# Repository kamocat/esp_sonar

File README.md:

# esp_sonar
Increased accuracy sonar by using esp32 for signal processing

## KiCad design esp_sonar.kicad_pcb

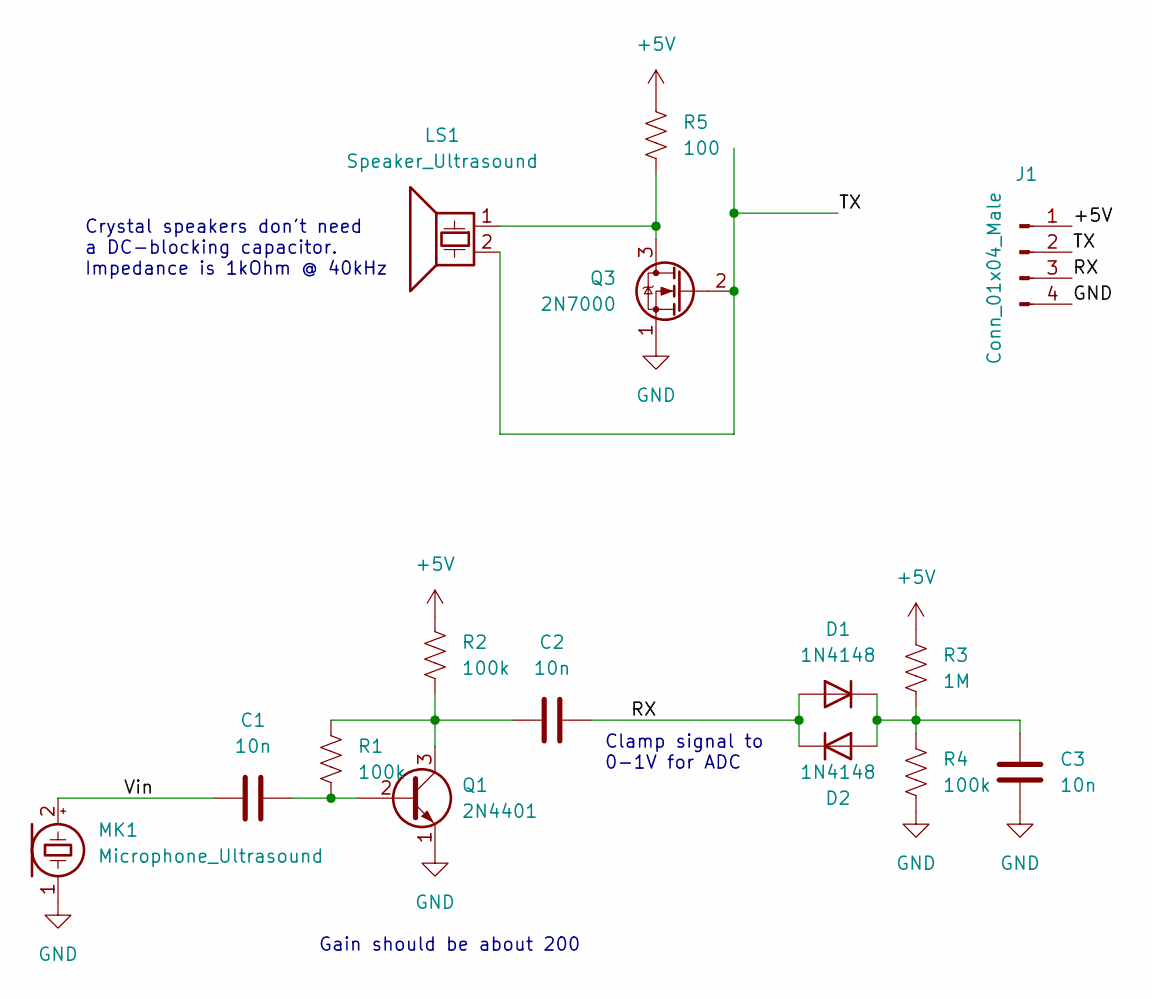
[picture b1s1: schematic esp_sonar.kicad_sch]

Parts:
C1, C2, C3: 10n; C_Disc_D4.7mm_W2.5mm_P5.00mm
D1, D2: 1N4148; D_DO-35_SOD27_P7.62mm_Horizontal
J1: Conn_01x04_Male; PinHeader_1x04_P2.54mm_Horizontal
LS1: Speaker_Ultrasound; PinHeader_1x02_P2.54mm_Vertical
MK1: Microphone_Ultrasound; PinHeader_1x02_P2.54mm_Vertical
Q1: 2N4401; TO-92_Inline_Wide
Q3: 2N7000; TO-92_Inline
R1, R2, R4: 100k; R_Axial_DIN0207_L6.3mm_D2.5mm_P10.16mm_Horizontal
R3: 1M; R_Axial_DIN0207_L6.3mm_D2.5mm_P10.16mm_Horizontal
R5: 100; R_Axial_DIN0207_L6.3mm_D2.5mm_P5.08mm_Vertical

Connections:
+5V: J1.1, R2.1, R3.1, R5.1
/RX: C2.2, D1.2 (A), D2.1 (K), J1.3
/TX: J1.2, LS1.2, Q3.2 (G)
/Vin: C1.1, MK1.2 (+)
GND: C3.2, J1.4, MK1.1 (-), Q1.1 (E), Q3.1 (S), R4.2
unnamed: C1.2, Q1.2 (B), R1.2
unnamed: C2.1, Q1.3 (C), R1.1, R2.2
unnamed: C3.1, D1.1 (K), D2.2 (A), R3.2, R4.1
unnamed: LS1.1, Q3.3 (D), R5.2

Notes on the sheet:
Clamp signal to 0-1V for ADC
Crystal speakers don't need a DC-blocking capacitor. Impedance is 1kOhm @ 40kHz
Gain should be about 200

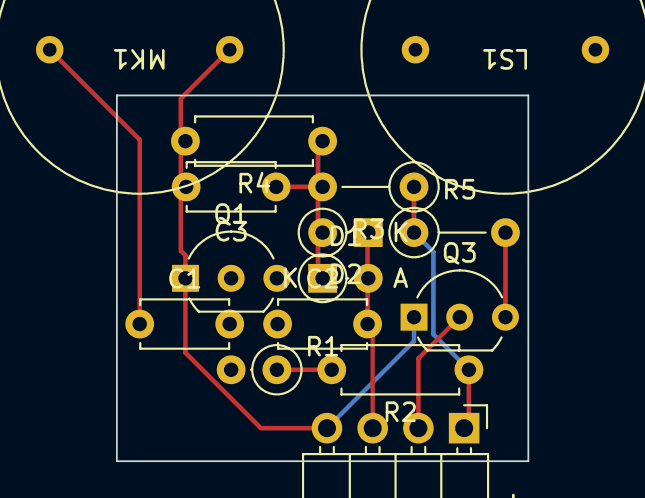
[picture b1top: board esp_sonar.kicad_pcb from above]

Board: 2 copper layers, 22.9 x 20.3 mm, 15 parts (0 on the bottom side), 9 nets.

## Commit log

2022-05-12 Output driver works, but is overkill
2022-05-12 Input amplification works, output in progress
2022-05-12 Protoboard layout
    Simplified driver to single-stage mosfet inverter
    Keeping the speakers off-board to maintain form factor
2022-05-12 TL072 gain-product bandiwdth is too low
2022-05-12 Improved layout
    Added R5 to prevent shoot-through when dle
2022-05-15 Replaced high-side mosfet with resistor to prevent shoot-through
